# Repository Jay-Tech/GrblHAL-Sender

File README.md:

# GrblHAL Sender

A cross platform sender application for grblHAL, built using Avalonia UI and .NET.

The goal was an application that runs on a cheap mini PC, with a UI designed to be touch monitor friendly and usable without a mouse or keyboard.
</br>
---

</br>
## Runs on a portrait monitor as well as a landscape one

</br>
The layout follows the screen's orientation on its own — a 1920x1080 monitor gets the
landscape arrangement, a 1080x1920 one gets a portrait layout built for that shape. There is
nothing to set; rotate the display and restart.

Portrait is a different arrangement rather than a squeezed copy. The status strip splits over
two rows, the 3D view takes the full width, and the controls gather into a block along the
bottom — DRO and MDI on the left, work offsets, spindle and macros in the middle, jog pad on
the right — so everything sits within thumb reach on a rotated touchscreen.

Both layouts are assembled from the same panels, so a change to the jog pad or the DRO turns
up in both.
</br>
## GrblHAL Setting supports export and import 

</br>
## Supports Serial, TCP, or WebSocket connection protocols.  Push and hold "Connect" to setup connection type and Auto Connect on app launch if desired 

</br>
## Double clicking any Text Fields brings up virtual keyboard

</br>
## Host local Web Server for remote file upload 

</br>
## Supports Wireless Controller
 
</br>
## Supports a Wireless Pendant
A handheld MPG - handwheel, touch screen, three buttons - over ESP-NOW or WiFi.
Firmware and hardware are a companion project:
[Jay-Tech/WirelessPendant](https://github.com/Jay-Tech/WirelessPendant). See
[Wireless Pendant](#wireless-pendant) below.
</br>
# Settings Overview
## App

</br>
## Rapid-ATC

</br>
## Wireless Gamepad
  
</br>
## Pendant

</br>
Enable it, pick a transport, and bound what it may ask the machine for. Four of
these fail quietly if set wrong - see [Settings that fail quietly](#settings-that-fail-quietly).
</br>
## Web Server

</br>
## Macro Download and Upload Supported

# Tool Change

What the sender does at an `M6` depends on the controller's `$341` tool change mode. The
mode is read from the machine, so the relevant controls appear on their own — there is
nothing to configure in the app to match it. Changing `$341` while connected is picked up
as well, without a reconnect.

| `$341` | Mode | What the sender does |
|---|---|---|
| 0 | Normal | Pauses at the `M6`, acknowledges it, waits for **Start**. Your program is responsible for stopping the spindle, moving to the change position and restoring afterwards. |
| 1 | Manual touch off | As above, plus a **Touch Off** button |
| 2 | Manual touch off @ G59.3 | As mode 1, and needs the [tool setter position](#tool-setter-position-g593) set |
| 3 | Automatic touch off @ G59.3 | Pauses; the controller probes for itself on **Start**. Needs the tool setter position set. |
| 4 | Ignore M6 | No pause — the tool number is recorded and the program continues |

In every mode except 4 the machine reports `Tool` state, the sender acknowledges it
(`0xA3`) once on entry, and the program continues only when you press **Start**. It behaves
like an `M0` pause: the acknowledgement does not resume anything.

## Streaming stops at the tool change

The sender holds the rest of the file back when it sends an `M6`, and does not resume until
the controller reports the change finished. This matters because grblHAL rejects g-code
while a tool change is pending (`error:40`) — anything already sitting in its receive
buffer past the `M6` is discarded rather than queued, which on a short file can be the
whole remainder of the program.

While the job is paused there you can **jog freely** and use **MDI**, including as many
moves as you like; the file position does not advance and nothing is lost. Macro and probe
buttons stay disabled, since those would interleave into the program.

## Manual touch off (modes 1 and 2)

A **Touch Off** button appears beside the `TOOL` banner while the job is paused. It sends
`$TPW`, which probes the new tool and applies its length offset.

Every tool change: stop at the `M6` → change the tool → jog it over the reference surface →
**Touch Off** → **Start**.

## Tool length reference — do this before the job

`$TPW` applies the *difference* between this probe and the previous one, so it needs a
baseline. Set it once per session under **Probe → Tool Setter**, with the tool you are going
to zero the stock from:

- **Probe Here** — probes straight down from where the machine is standing; jog the tool
  over the setter first
- **Probe at G59.3** — retracts Z to machine zero, travels to the stored tool setter
  position, descends and probes

Either way the reference is set only if the probe actually makes contact. Then zero on the
stock and start the job, and every tool change from there needs nothing but **Touch Off**.

The panel says whether the controller currently holds a reference. On a good probe the tool
is backed off the trigger, and **Probe at G59.3** also returns to the X/Y it started from —
retracting Z to machine zero on the way and leaving it there, since the height it came from
may be down in the work.

> `$TLR` must follow a *successful* probe. Sent before one, or after a failed one, it clears
> the reference instead of setting it — which is why the app only issues it on a good probe.

Re-running it re-bases the datum onto whatever was last probed, so only do it deliberately —
after moving the tool setter, or re-zeroing against a different tool.

Touch plate thickness plays no part in this. The offset is a differential against the same
surface, so the thickness cancels out. Thickness only matters for setting workpiece Z zero,
which is a separate operation in the **Probe** dialog.

## Tool setter position (G59.3)

</br>
Modes 2 and 3 drive to the `G59.3` offset to reach the tool setter. Set it under
**Probe → Tool Setter**: jog the machine where you want it and store the position. X/Y and
Z are stored separately so neither overwrites the other by accident, and the stored value is
read back from the controller after each change so you can see what actually took effect.

> **The stored Z is where probing starts, not the tool setter surface.** The controller
> moves all three axes to `G59.3` and then probes downward by `$342`. Store Z at a safe
> clearance height above the setter — high enough for your longest tool, and no further
> above the setter than `$342`.

## Macro messages

Anything the controller says in words — including `(debug, ...)` output from a tool change
macro — is shown in the job panel, not only in the console. A macro that stops on
"manually unload the tool and unlock to continue" says so on screen.

# Probing

Every cycle probes twice: a fast pass at **Search Rate** to find the surface, then a slow one
at **Latch Rate** to measure it. **Distance** is how far a probe may travel looking for the
surface, and **Latch Dist** is how far it backs off between the two passes.

Probe moves are commanded in whatever units the display is set to, and the parser is handed
back the unit it was in when the cycle finishes.

Only the fields a cycle actually reads stay enabled, so what is greyed out is not being used.

## Probe type

| | |
|---|---|
| **Touch plate** | Work Z zero ends up the plate's thickness below where it triggered. |
| **3D probe** | **Diameter** compensates edge touches on the corner and centre cycles, and corrects the size they report. It plays no part in a Z probe — the ball meets a flat surface with its underside, directly beneath its centre, so where it triggers *is* the surface. |

## Z height

Position the probe above the surface and press **Probe Z**. Work Z zero is set at the surface,
and the stylus lifts clear by **Latch Dist** rather than being left resting on the work.

## Corner

Bring the probe to the corner, above the top face, and pick the corner that matches. Each leg
lifts to **Clearance Height**, moves clear of the stock on the axis it is about to probe while
stepping *in* on the other, drops by **Probe Depth**, and probes back toward the face. It
finishes lifted and standing over the corner it measured, which is now X0 Y0.

> **Probe Depth is measured from where you parked the stylus, not from the top of the stock.**
> If you sit 2mm above the face and want to touch 3mm down the side, Probe Depth is 5. Too
> shallow and the probe sweeps over the top of the edge and touches nothing.

The stand-off is Clearance Height, so Distance has to be comfortably larger than it for the
probe to reach the face.

## Center finder

**Bore** and **Rectangle** work from inside a hole or pocket. Position the probe roughly in
the middle, at the height you want it to touch at — these cycles never move Z, so Clearance
Height and Probe Depth do nothing and are greyed out. Distance has to cover the radius plus
however far off centre you started. Between legs the machine returns to the point you began
at, so a generous Distance is safe.

**Boss** and **Rect Boss** work from outside. Position the probe over the middle of the
feature and above its top face. Each leg stands off by half the approximate size plus
Clearance Height, drops by Probe Depth, and probes inward. A round boss takes one size; a
rectangular one takes a width and a height separately.

> **Keep Clearance Height larger than your eyeballing error.** Starting off centre adds to the
> stand-off on the far side and takes it away on the near side, so being out by more than the
> clearance puts the stylus over the feature when it drops. Under-estimating the approximate
> size eats the same margin. Over-estimating is safe — the probe simply travels further.

Y is probed from the X you started at rather than the measured centre. That is exact for a
rectangle, where a flat face reads the same anywhere along it, and leaves a small error on a
bore or boss if you started well off centre. Run it twice if that matters.

## When a probe misses

The cycle stops at the first missed contact rather than carrying on from a position that means
nothing, and says which datum it did not set. Nothing is written on a failure. A tool length
reference is the one worth spelling out: `$TLR` is not sent, so whatever reference the
controller was holding is still intact.

# G-code Events

</br>
Pre and post commands can be injected around any g-code event, configured under
**Utility → G-code Events**. The original use case is lifting a dust shoe out of the way for
a tool change or a homing cycle, but nothing about it is specific to that.

Each rule has a trigger and the commands to wrap it with:

- **Trigger** — one or more commands, comma separated, e.g. `$H,G28`. A `$` command matches
  as a prefix, so `$H` also catches `$HX`. A single word matches by value, so `M6` catches
  `T3M6` and `M06` but not `M61`.
- **Pre / Post** — commands to send before and after the trigger, separated by `|` for more
  than one. `{T}` inserts that word's value from the triggering line, `{LINE}` the whole line.
- **Job / MDI** — whether the rule applies to a streamed file, to commands you issue by
  hand, or both.

Rules are applied when a file is loaded, so reload the file after editing one.

## Getting the timing right in a job

grblHAL executes `M64`/`M65` when it *parses* them, which during a job is well ahead of the
cutting point — so a plain `M65P0` before an `M6` fires many blocks early, while the spindle
is still down and cutting.

A dwell forces the planner to drain before continuing, so putting one *first* moves the
output change to the right moment:

| | |
|---|---|
| `M65P0\|G4P0.2` | lifts early, then waits — wrong |
| `G4P0.1\|M65P0` | waits for the cut to finish, then lifts — right |

Aux output buttons follow these commands wherever they come from, so a rule that toggles a
pin moves the matching button too.

# Shop Outputs

</br>
The sender can switch relays for shop lights, dust collection — anything you would otherwise
reach over and flip. Configured under **Utility → GPIO**, and off by default: nothing is
driven until you enable it.

This is for convenience, not safety. E-stop and safety door belong hardwired to the
controller, where they do not depend on a userland app being responsive. Nothing here is
time-critical either — the outputs settle in the second or so after the machine state
changes, which is fine for a vacuum and useless for an interlock.

Worth knowing why this exists alongside the controller's own aux outputs: those are driven by
`M62`/`M64`, which grblHAL executes when it *parses* them, well ahead of the cutting point
during a job. That is why the [G-code Events](#getting-the-timing-right-in-a-job) section
needs dwell-first ordering. A shop output is not in the g-code stream at all, so "run the vac
while the spindle is cutting, then for fifteen seconds after" needs no such trickery.

## Where the outputs live

| Device | Needs | Notes |
|---|---|---|
| **PiHeader** | A Raspberry Pi | The Pi's own 40-pin header. No extra hardware. |
| **UsbSerial** | A microcontroller on USB | Works on any host the app runs on — mini PC, Mac, or a Pi. |

The USB option exists because the header option only ever serves installs that run on a Pi.
Both behave identically once configured; everything below applies to either unless it says
otherwise.

## Off / Auto / On

Each output is a button in the bottom-left of the workspace, above the controller's aux
output buttons. Tapping it cycles the mode. The ring around the button shows whether the
relay is actually energised, which is not the same thing as the mode — an output sitting in
Auto reads `AUTO` whether or not it happens to be on right now.

| Mode | Behaviour |
|---|---|
| **Auto** | Follows the machine. Skipped in the cycle for outputs with no follow source. |
| **On** | Held on regardless of the machine. This is the one for cleanup before and after a job. |
| **Off** | Held off. Takes effect immediately — it does not wait out the off delay. |

Unlike the aux output buttons these stay live while the controller is disconnected, because
running the vacuum with the machine idle or unplugged is most of the point of the manual mode.

## What Auto follows

| Follows | Source |
|---|---|
| **Spindle** | The controller's accessory (`A:`) field |
| **Connected** | Whether the controller is connected — reasonable for lighting |
| **None** | Manual only; the output has no Auto mode |

Spindle state is taken from the status report rather than by watching for `M3`/`M5` in the
stream, so it reflects what the machine is actually doing. It picks up a spindle you started
by hand from the console, and it stays honest when a job aborts part way through, where the
file position tells you nothing useful.

## Spindle threshold — for ATC tool changes

**Min RPM** is the speed at or above which the spindle counts as running. Leave it at `0` and
any spindle-on state qualifies.

It exists for automatic tool changers. A RapidChange ATC and similar turn the spindle at a
low speed to thread and unthread the holder — a genuine spindle-on state with no cutting and
no chips. Without a threshold the dust collector fires at every tool change. Set Min RPM
above your changer's speed and below your cutting speed, and tool changes stop triggering it.

The comparison uses the *programmed* speed — the `S` word from the status report — not tacho
feedback. That steps cleanly when a macro commands a speed, rather than sweeping through the
threshold on every spin-up and spin-down.

Speed is watched as well as direction, which matters at the end of a change: the program
returns to cutting speed with the spindle never stopping, so the direction does not change
across it. Dropping back under the threshold mid-job behaves like the spindle stopping and
goes through the off delay, so a change that fits inside the delay window never moves the
relay at all.

> The threshold reads whatever `S` value is currently in force, so a tool change macro that
> sets a low `S` and does not restore it will hold the output off until the program commands
> a speed again.

## Off delay

An output in Auto stays on for **Off Delay** seconds after its source goes inactive. This is
doing two jobs. It clears the hose of chips still in flight after a cut, and — more
importantly — it stops a program full of tool changes and `M5`/`M3` pairs from dropping and
re-closing a contactor every few seconds. Any fresh demand inside the window cancels the
pending switch-off, so a run of tool changes collapses into one continuous run.

Fifteen seconds is a sensible starting point. An explicit **Off** ignores the delay entirely.

## Wiring

On a Pi, pins are **BCM numbers**, 2–27. Avoid 2/3 (I²C, permanently pulled up), 7–11 (SPI)
and 14/15 (UART); 17, 22, 23, 24, 25, 27 are all clean, and the **Add Output** button hands
out unused ones in that order.

On a USB device, pins are that board's own numbering — `GP` numbers on a Pico — and the valid
range is reported by the device itself rather than assumed.

**Prefer an active-high relay board.** BCM 9–27 boot with a pull-down, so an active-high
board reads *off* while the Pi boots, while the app is starting, and after it exits or
crashes — the fail-safe state costs nothing. An active-low board inverts all of that and
wants an external pull-up to stay safe. Set **Active Hi** to match whichever you have.

Do not drive a relay coil from a pin directly; use an opto-isolated module, a MOSFET driver
or an SSR. And size the switching for the load — a shop vacuum's inrush will weld the
contacts of a generic 10 A relay board sooner or later, so drive a proper contactor with it.

## Pi header setup

The header GPIO is reached through libgpiod. Installing the tools package pulls the right
runtime library whichever release you are on, which matters because the library package was
renamed between Debian releases (`libgpiod2` on Bookworm, `libgpiod3` on Trixie):

```
sudo apt install gpiod
sudo usermod -aG gpio $USER
```

Log out and back in for the group to take effect. `gpiodetect` should report the 40-pin
header as `gpiochip0 [pinctrl-rp1]` on a Pi 5.

If the app cannot reach the hardware it says so on the GPIO config tab rather than failing
silently or crashing — the message is the underlying error, so it will tell you whether it is
a driver or a permissions problem. With no device reachable the outputs still appear and
toggle but switch nothing, which keeps the app usable for development.

## USB device setup

The device runs the PICOGPIO protocol, specified in
[docs/pico-gpio-protocol.md](docs/pico-gpio-protocol.md). A MicroPython reference
implementation for a Raspberry Pi Pico is in [firmware/pico/main.py](firmware/pico/main.py) —
about a hundred lines, and enough to use in earnest.

Flash MicroPython onto the board, then copy the script to it as `main.py` so it runs on boot
and owns the USB serial port instead of the REPL:

```
pip install mpremote
mpremote connect COM10 fs cp firmware/pico/main.py :main.py
mpremote connect COM10 reset
```

Then pick **Device: UsbSerial** and select the port. **Close any IDE connected to the board
first** — a serial port can only be held by one program, and Thonny in particular keeps the
handle after you disconnect, which shows up as "access is denied". **Reconnect** retries
without restarting the app, and also covers unplugging the device mid-session.

The app never scans ports. A grblHAL controller and a Pico both enumerate as `/dev/ttyACM*`
on Linux and are indistinguishable by name, so the port is always chosen explicitly and
nothing is written until the device identifies itself.

### The device watchdog

The protocol requires the device to drive every output inactive if the host stops talking to
it — five seconds in the reference implementation. This covers what the app cannot: the
application crashing, the cable being pulled, or the host sleeping while USB power stays up.
A host-side "turn everything off on exit" only works when the exit is orderly.

That makes a USB device arguably safer than the Pi header, where an app that dies leaves the
pins to their boot-time pull-down.

## Behaviour worth knowing

Losing the connection drops any output following the spindle. Status reports stop arriving
when the link goes down, so the last known spindle state is stale — left alone, a spindle
that happened to be running at that moment would hold the dust collector on indefinitely.

Closing the app drives every output off before it exits, so quitting cannot leave the vacuum
running. The mode each output was left in is saved, with one exception: an output that
follows something never comes back **On** after a restart. Returning from a power cut with
the dust collector latched on is not what anyone means by remembering a setting. Manual-only
outputs do restore On, so shop lights come back as you left them.

# Wireless Pendant

A handheld MPG pendant - handwheel, touch screen, three buttons - that talks to
this application rather than to the controller. The firmware, the hardware and
the printed enclosure are a companion project:
**[Jay-Tech/WirelessPendant](https://github.com/Jay-Tech/WirelessPendant)**.

It goes through the sender deliberately. grblHAL's telnet server accepts exactly
one client and this app already holds it, so a pendant cannot have a session of
its own; and on an SLB the controller sits on an isolated subnet with no route
from the shop WiFi. Coming through the sender works with any controller and keeps
one arbiter of the command queue, which is what GRBL needs regardless.

## Two transports, and both run at once

| | |
|---|---|
| **ESP-NOW** | the pendant talks to a small receiver board plugged into this PC, which appears here as a serial port. No network, no credentials |
| **WiFi** | the pendant joins the shop network and opens a TCP session to the port set on the Pendant tab |

Both carry the same newline-delimited JSON, so nothing above the transport knows
which one a pendant arrived on, and naming a receiver port does not disable the
network listener.

**One pendant drives the machine at a time, and the newest wins.** That is not
about arbitrating between two operators - it is about one operator whose pendant
has appeared twice. Over WiFi the older connection is usually a stale half-open
socket left by a lost link, which TCP can take minutes to give up on; over
ESP-NOW it is a handheld just switched on while the WiFi one is still nominally
connected. Refusing the newcomer in either case locks the operator out of the
machine while a dead connection times out.

## The receiver's port is never scanned for

Pick it explicitly. A grblHAL controller and a receiver board both enumerate as
anonymous USB serial devices and cannot be told apart by name, and pendant JSON
written at a controller is at best noise in its console. Leave it on *(none)* if
no receiver is fitted; the WiFi listener still runs.

## Settings that fail quietly

Most of the Pendant tab explains itself. These four do not:

| Setting | Default | Why it matters |
|---|---|---|
| **Max feed rate** | 12000 | Set this to the machine's own maximum jog rate. The pendant already limits itself per axis and per step, and 12000 is the most it can ever ask for - so anything lower **silently discards feed the operator asked for**. A previous default of 5000 clamped both coarse steps, which is felt as the wheel going heavy near the top of its range and reported as nothing. |
| **Min gap between jogs** | 10 ms | Must stay **below** the pendant's 20 ms tick. Set equal, the two free-run and beat against each other: some windows carry two messages and some carry none, and an empty window is a gap the machine decelerates into. Set above, messages merge back into the long blocks the short tick exists to avoid, which halves the count the planner can chain - and chaining is what holds a feed. This is also the only place backpressure can be applied, since the pendant cannot see the controller's planner. |
| **Max jog per message** | 50 mm | Bounds a corrupted detent count, and clamps rather than discards. At a 20 ms tick and the 12000 mm/min ceiling a dispatch window legitimately carries 4 mm, so this leaves an order of magnitude of headroom. |
| **Allow pendant to zero an axis** | off | Zeroing rewrites the work offset. Off by default so a mis-hit button on a handheld cannot lose your datum. |

**Enabling the pendant takes an app restart.** Two more worth knowing about:

- **Client timeout**, 15 s, stands the pendant down when it goes quiet. The
  pendant pings every few seconds, so silence means it has gone away without
  saying so - a case TCP alone can take minutes to notice, and a serial receiver
  cannot notice at all, since its port stays open whether or not a handheld is
  switched on. Zero disables it.
- **Echo pendant jogs to console** is diagnostic only. Jogs arrive fifty times a
  second, which fills the console to its cap within seconds and then costs a UI
  update on every status tick - felt as jerk partway through a long move.

## The receiver's DTR and RTS are configurable, and the board decides

Behind a USB-UART bridge these are not flow control at all: they are wired to EN
and IO0 through the auto-reset circuit, so driving them on open resets the chip
or drops it into its bootloader. An ESP32-S3 has native USB and no such circuit,
but a firmware using TinyUSB CDC may read DTR as "a terminal is attached" and go
quiet without it. The two failure modes want opposite settings, which is why this
is configuration rather than a constant.

Change them only against an observed symptom - a receiver that wedges when the
sender starts, or one that opens cleanly and then never says anything.

# Testing status

Runs on Windows and on Linux including the Pi 5, on landscape and portrait displays.

Verified on hardware:
- The portrait layout on a 1080x1920 screen, and the landscape one after the panels were
  refactored to be shared between the two
- Tool change streaming — the job holds at the `M6`, survives jogging during the pause, and
  resumes cleanly on **Start**
- Manual touch off (`$341=1` / `2`) — the **Touch Off** button and `$TPW`, including jogging
  to the setter and back mid-change
- Automatic touch off (`$341=3`)
- `M6T<n>` from the MDI with no file loaded
- Tool length reference and tool setter position (`G59.3`), including the return to the X/Y
  the probe started from
- Changing `$341` while connected — the controls follow without a reconnect
- G-code event injection around a tool change, including the dwell-first ordering
- GPIO shop outputs on a Pi 5 — a relay on BCM 17 following the spindle in Auto, and the
  manual On/Off override, with no spurious activation across two boot cycles
- Shop outputs over USB — a Pico running the MicroPython reference firmware, driven from a
  Windows host: identify handshake, pin claim and switching
- Serial connection and reconnection
- Single instance guard on Linux
- The probe cycles with a 3D probe — workpiece Z zero, all four corners, and centre finding
  inside a bore and outside a boss

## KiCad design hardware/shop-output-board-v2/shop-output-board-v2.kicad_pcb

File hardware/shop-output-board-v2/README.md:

# Shop Output Board v2

> ### On the shelf as of 2026-08-06 — see [commercial-alternatives.md](../commercial-alternatives.md)
>
> Bought Pico relay boards cover the shop-outputs use case for a fraction of what this costs
> to build, with the relays already on them and an enclosure round the outside. This board was
> routed, verified and had its JLCPCB files prepared before that turned up — all of which is
> still here and still correct. It just is not the thing to order.
>
> Worth knowing if you come back to it: the design is sound, `JlcLab/` is ready bar the LCSC
> codes and F1 sourcing, and **it has never been bench-tested**. Start at
> [bench-test.md](../shop-output-board/bench-test.md) if that ever changes.

Four-channel opto-isolated high-side switch board. **70 × 92 mm against v1's 150 × 115 —
64% less area**, same circuit per channel.

**Generated and placed, not routed.** DRC is clean on the placement; the routing is the work
left to do, exactly as v1 was at this stage.

## What changed from v1, and what did not

**Unchanged: the entire channel circuit.** Same optocoupler, same AO3401A, same 8.2 V gate
clamp, same resistor values. That is the point — [v1's bench-test procedure](../shop-output-board/bench-test.md)
validates this board too, and the one part of the design nobody has watched work does not get
disturbed by a packaging exercise.

| | v1 | v2 |
|---|---|---|
| Channels | 8 | 4 |
| Board | 150 × 115 mm | **70 × 92 mm** |
| Parts | 84 | 47 |
| Output terminals | two 6-way | one 6-way (4 out + 2 gnd) |
| Bulk cap C1 | 100 µF, 8 × 10.5 mm | 47 µF, 6.3 × 7.7 mm |
| MCU | socketed Pico | socketed Pico — *unchanged* |
| F1 | 1812, 1.1 A / 24 V | same |

**The Pico stays.** Swapping it for a thumb-sized RP2040 module was the original motivation
for v2 and it turned out to be worth almost nothing: at four channels the channel bank is
51.4 mm wide and a Pico's pad span is 48.3 mm, so the Pico already fits inside the width the
channels demand. On height it buys 3.78 mm. See [v2-layout.md](../shop-output-board/v2-layout.md)
for the full working. Keeping it means no new footprint, no pin map, no firmware change.

## The channel, rearranged

This is where the height saving comes from. v1 stacks all seven isolated-side parts in one
column 35 mm tall; v2 splits them into two sub-columns grouped by **net**:

```
                 cx-4              cx+4
  y=41.19          ▀▀▀ opto pins 3,4 ▀▀▀      (centreline)
  y=44      ═══════════ V+ rail ═══════════
  y=47             Q                 R2       Q source → rail; R2 → opto above
  y=51             R3                D
  y=55             R4                R1
  y=59             LED
```

**Left column is everything touching `OUT`, right column is everything touching `GATE`.**
They meet only at Q, which is why Q sits at the top of the left column — its source reaches
the rail in 2 mm, its gate faces right toward the gate column, and its drain has a clear run
straight down its own column to the terminal. R2 sits opposite it, directly under the
optocoupler it feeds.

Channel height: **19 mm, against v1's 35 mm.**

## Regenerating

```
python generate_schematic.py
kicad-cli sch erc --output erc.rpt --severity-error shop-output-board-v2.kicad_sch
kicad-cli sch export netlist --output netlist.net shop-output-board-v2.kicad_sch
python verify_netlist.py

python generate_pcb.py
kicad-cli pcb export ipcd356 --output pads.d356 shop-output-board-v2.kicad_pcb
python verify_pcb.py
kicad-cli pcb drc --refill-zones --output drc.rpt --severity-error shop-output-board-v2.kicad_pcb
```

Channel count comes from `CHANNEL_GP` in `generate_schematic.py` — shortening that list is
the whole change. Everything else derives from it.

`generate_pcb.py` has **no `--route` flag**. v1 carried one that never got past 113 DRC
violations; a half-routed board is worse to inherit than an unrouted one, so it is not
carried forward.

## State

| | |
|---|---|
| Schematic | generated, ERC clean (0 violations) |
| Netlist | 58 nets, 47 parts, all assertions pass |
| Placement | generated, 99 pads match KiCad's own coordinates to 0.05 mm |
| Barrier | 16 opto pads correct side; **0 traces, 0 vias, 0 zone vertices** in y=34–39 |
| Routing | **done by hand** — 198 segments, 11 vias, 0 unconnected |
| Mounting | 3 × Ø3.2 mm NPTH at (4,4), (4,88), (66,4), each with a Ø7.6 copper keepout |
| DRC | 15 violations, **all `output net spacing`** — see below |
| Bench verification | none — inherited from v1, which has not been tested either |

## Mounting holes and the isolation barrier

The holes straddle both domains: (4,4) and (66,4) sit in the `PICO_GND` pour, (4,88) in
`ISO_GND`. Mounted on a metal panel with metal standoffs, the chassis ties all three together
— so if any screw head reaches the pour it is sitting on, **the two ground domains are
bridged and the isolation this board exists for is gone.**

As first routed, copper came within 0.34–0.50 mm of the hole edges, which every standard M3
head overlaps:

| Hardware | Head reach | Was | Now |
|---|---|---|---|
| M3 socket cap Ø5.5 | 2.75 mm | contact | clears 1.04 mm |
| M3 pan head Ø5.6 | 2.80 mm | contact | clears 0.99 mm |
| M3 countersunk Ø6.0 | 3.00 mm | contact | clears 0.79 mm |
| M3 + flat washer Ø7.0 | 3.50 mm | contact | clears 0.29 mm |

Fixed with a **Ø7.6 mm copper keepout** (48-gon, R3.8) on both layers at each hole, blocking
pour, tracks and vias. Copper now sits 3.79 mm from each hole centre, measured on a
zone-refilled Gerber plot rather than the stored fill.

**DRC cannot catch this class of fault** — it has no concept of a screw head. If you move a
mounting hole, re-check it by hand.

The holes were also Ø3.00, which is zero clearance for an M3 (its major diameter *is* 3.0 mm,
so the screw will not pass). Now Ø3.2, the standard close fit.

## Net classes: set them, or DRC is lying to you

`shop-output-board-v2.kicad_pro` carries `Logic` and `Isolated` as `netclass_patterns`. The
custom rules in `shop-output-board-v2.kicad_dru` key on exactly those names.

Until they were set, **DRC reported 0 violations on a board with 19 of them**, because every
custom rule silently matched nothing. The barrier happened to be clean — verified by hand —
but nothing was checking it. Confirmed armed by injecting a deliberate barrier-crossing trace
into a scratch copy: caught as `rule 'isolation barrier' clearance 5.0000 mm; actual 0.1250 mm`.

If you ever edit net classes in Pcbnew, remember **File → Save Project**, not Ctrl+S.

## The 15 remaining violations

All are the `output net spacing` rule: 0.20 mm actual against the 0.40 mm the rule asks for,
across four pairs where the outputs fan into J2.

| Pair | Region |
|---|---|
| OUT1 ↔ OUT2 | x 19–60, y 63–78 |
| OUT1 ↔ V+ | x 4–50, y 54–63 |
| OUT2 ↔ OUT3 | x 35–60, y 54–78 |
| OUT3 ↔ OUT4 | x 52–61, y 55–71 |

This is a **margin** rule, not a correctness one — it exists to give the output nets room
against inductive kick from relay coils at the far end of the wiring. The board is
electrically fine at 0.20 mm. Either re-route that fan-in with 0.4 mm spacing (there is room:
0.5 mm tracks on a 3.81 mm terminal pitch need only 0.9 mm), or relax the rule deliberately
and write down why. Do not leave it failing silently.

## Before this goes anywhere

**v2 inherits v1's entire channel circuit, so a v1 bench failure is a v2 failure.** There is
no sense routing this, let alone fabbing it, until one channel has been proven on a
breadboard. That procedure is [bench-test.md](../shop-output-board/bench-test.md).

The indicator LED polarity bug found in v1 on 2026-08-05 is fixed here from the start — the
node from R4 lands on pin 2 (anode), and `verify_netlist.py` asserts it in that direction.

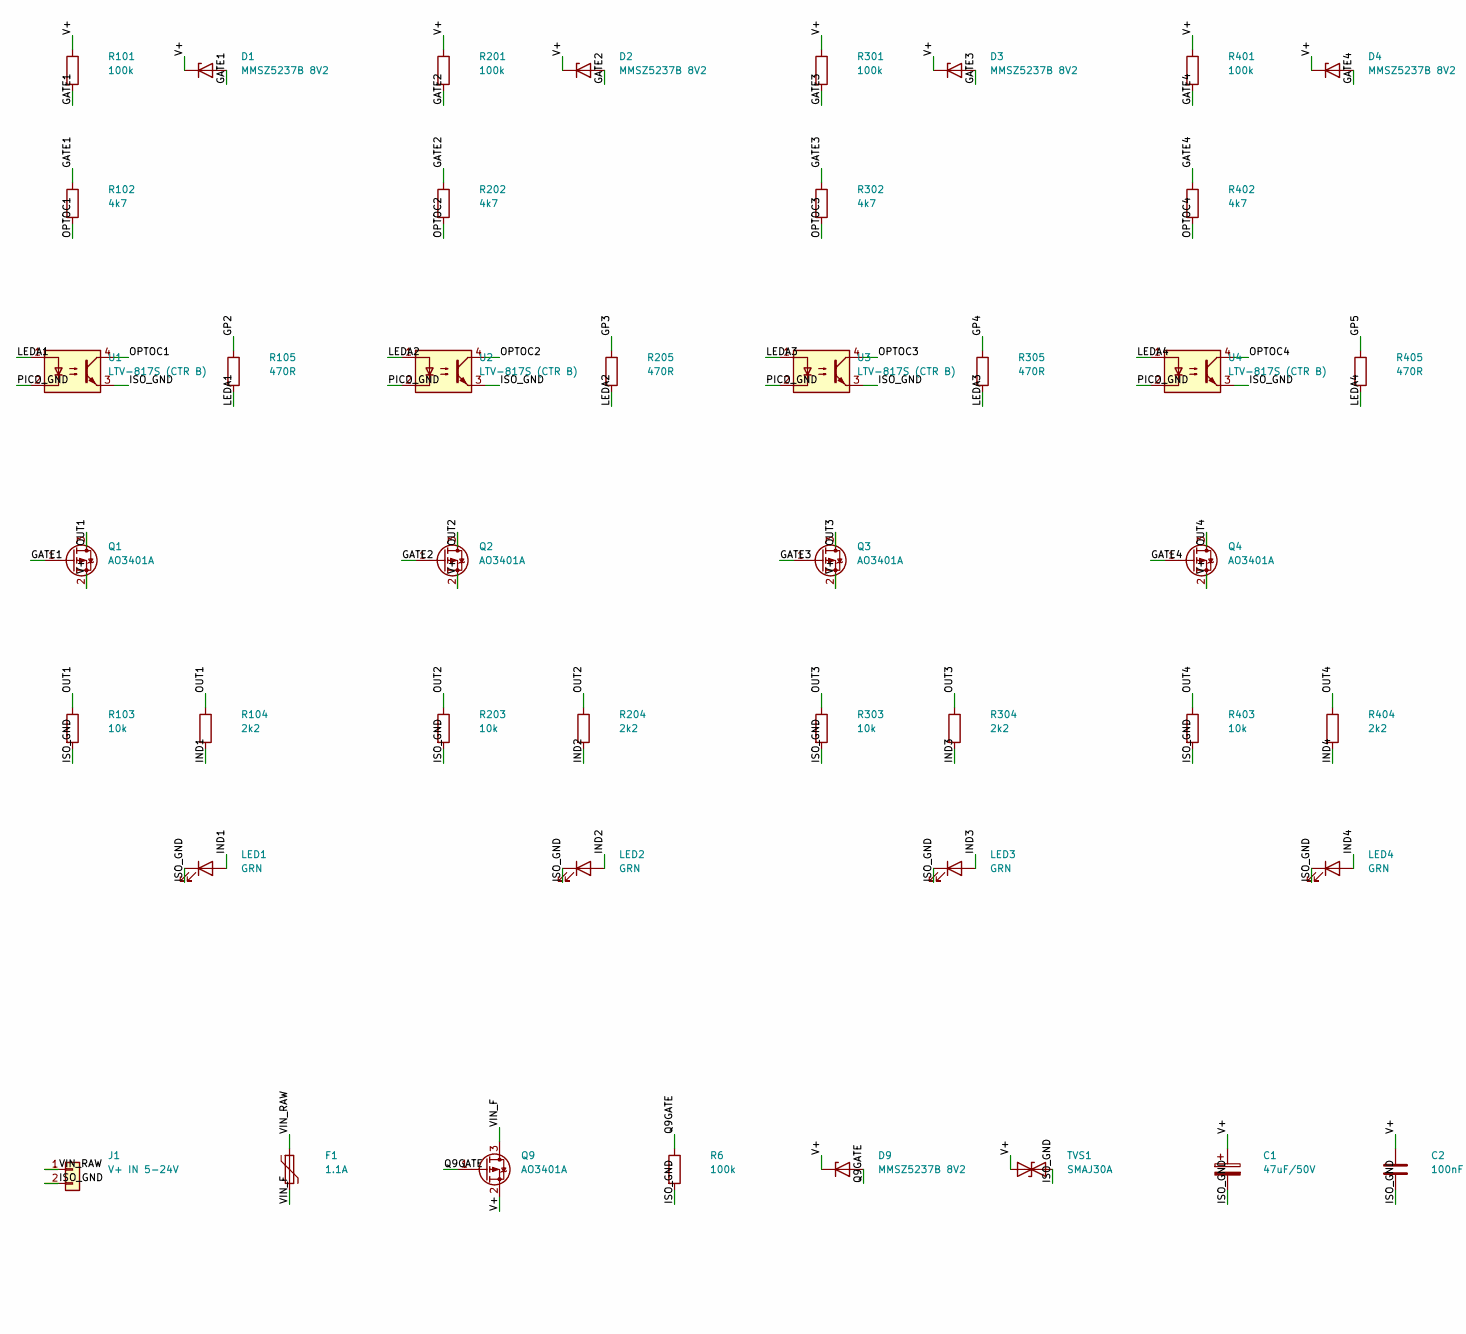
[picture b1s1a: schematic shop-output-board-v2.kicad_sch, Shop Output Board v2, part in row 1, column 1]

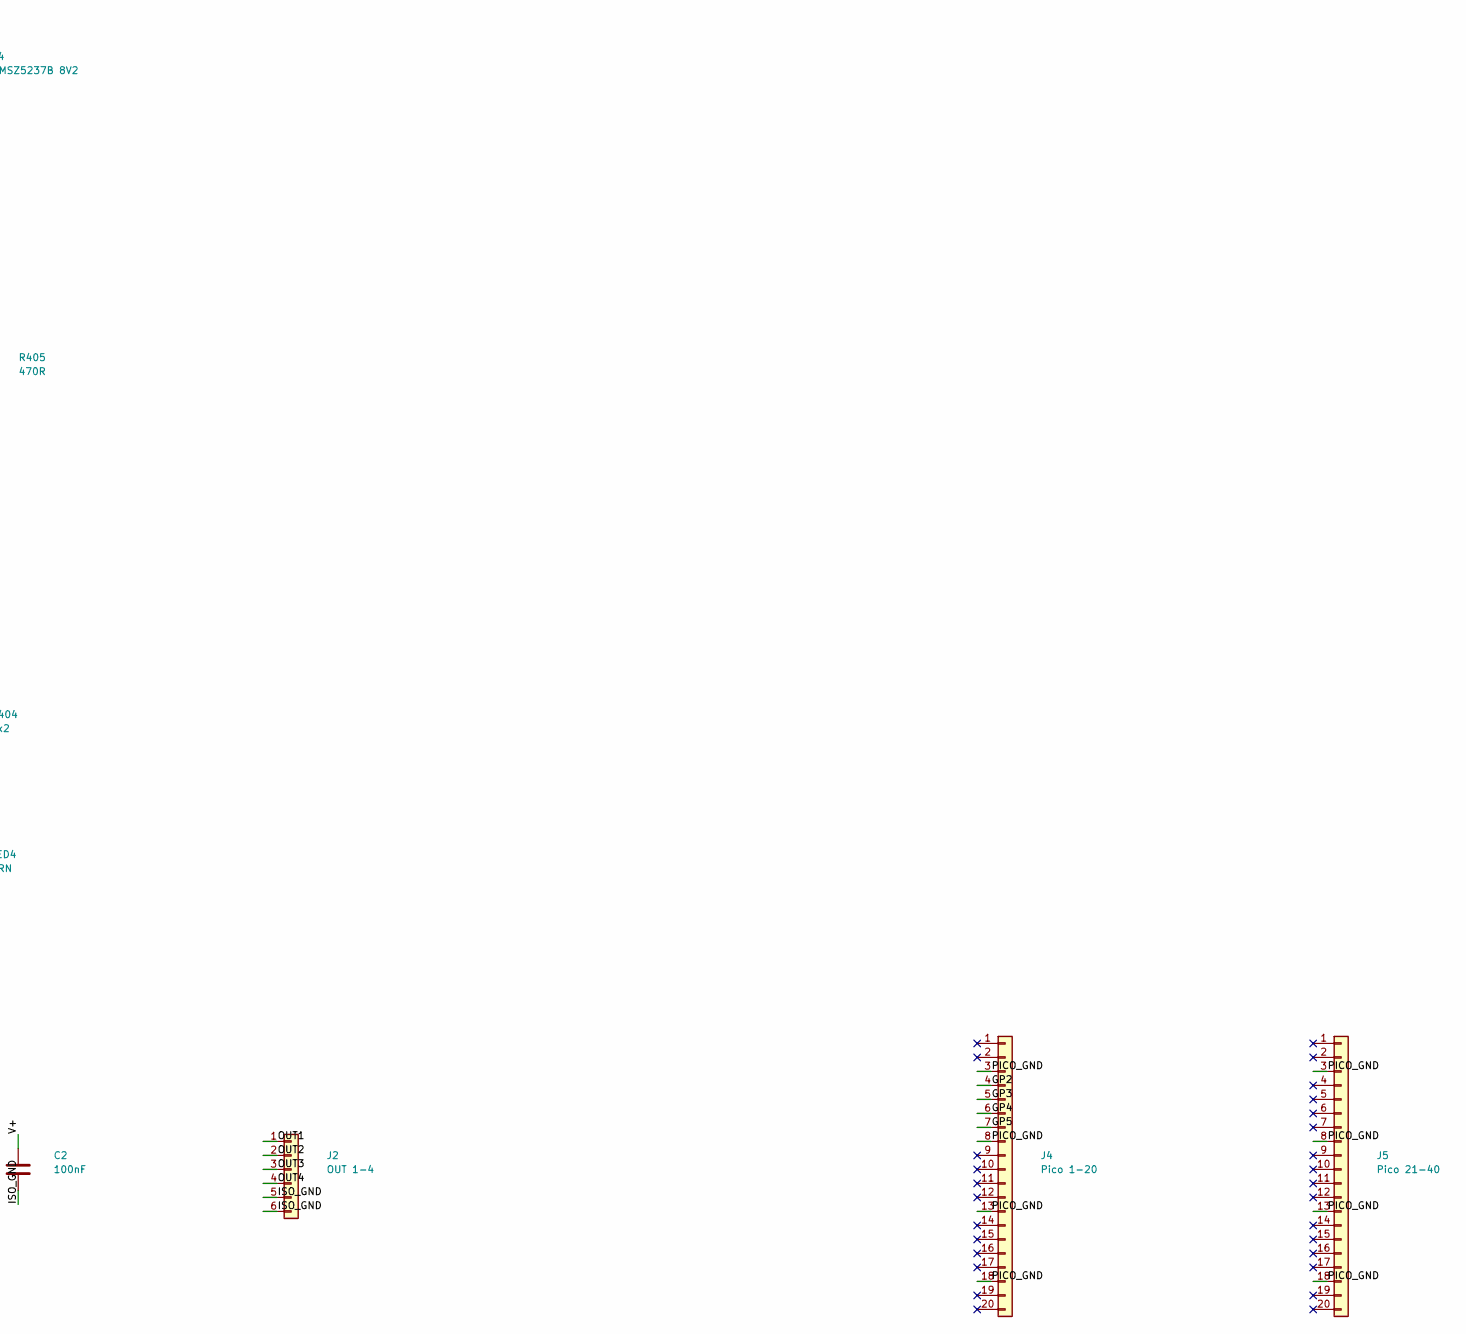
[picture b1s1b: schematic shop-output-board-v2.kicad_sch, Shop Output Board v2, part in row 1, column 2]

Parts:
C1: 47uF/50V; CP_Elec_6.3x7.7; MPN EEE-FK1H470XP
C2: 100nF; C_0805_2012Metric; MPN CL21B104KBCNNNC
D1, D2, D3, D4, D9: MMSZ5237B 8V2; D_SOD-123; MPN MMSZ5237B-7-F
F1: 1.1A; Fuse_1812_4532Metric; MPN MF-MSMF110/24X-2
J1: V+ IN 5-24V; TerminalBlock_Phoenix_MKDS-1,5-2-5.08_1x02_P5.08mm_Horizont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; MPN 1729128
J2: OUT 1-4; TerminalBlock_Phoenix_MKDS-1-6-3.81_1x06_P3.81mm_Horizontal; MPN 1727052
J4: Pico 1-20; PinSocket_1x20_P2.54mm_Vertical; MPN PPTC201LFBN-RC
J5: Pico 21-40; PinSocket_1x20_P2.54mm_Vertical; MPN PPTC201LFBN-RC
LED1, LED2, LED3, LED4: GRN; LED_0805_2012Metric; MPN LTST-C170KGKT
Q1, Q2, Q3, Q4, Q9: AO3401A; SOT-23; MPN AO3401A
R6, R101, R201, R301, R401: 100k; R_0805_2012Metric; MPN RC0805FR-07100KL
R102, R202, R302, R402: 4k7; R_0805_2012Metric; MPN RC0805FR-074K7L
R103, R203, R303, R403: 10k; R_0805_2012Metric; MPN RC0805FR-0710KL
R104, R204, R304, R404: 2k2; R_0805_2012Metric; MPN RC0805FR-072K2L
R105, R205, R305, R405: 470R; R_0805_2012Metric; MPN RC0805FR-07470RL
TVS1: SMAJ30A; D_SMA; MPN SMAJ30A
U1, U2, U3, U4: LTV-817S (CTR B); SOP-4_7.5x4.1mm_P2.54mm; MPN LTV-817S-TA1-B

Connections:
GATE1: D1.2 (A), Q1.1 (G), R101.2, R102.1
GATE2: D2.2 (A), Q2.1 (G), R201.2, R202.1
GATE3: D3.2 (A), Q3.1 (G), R301.2, R302.1
GATE4: D4.2 (A), Q4.1 (G), R401.2, R402.1
GP2: J4.4, R105.1
GP3: J4.5, R205.1
GP4: J4.6, R305.1
GP5: J4.7, R405.1
IND1: LED1.2 (A), R104.2
IND2: LED2.2 (A), R204.2
IND3: LED3.2 (A), R304.2
IND4: LED4.2 (A), R404.2
ISO_GND: C1.2, C2.2, J1.2, J2.5, J2.6, LED1.1 (K), LED2.1 (K), LED3.1 (K), LED4.1 (K), R6.2, R103.2, R203.2, R303.2, R403.2, TVS1.2 (A2), U1.3, U2.3, U3.3, U4.3
LEDA1: R105.2, U1.1
LEDA2: R205.2, U2.1
LEDA3: R305.2, U3.1
LEDA4: R405.2, U4.1
OPTOC1: R102.2, U1.4
OPTOC2: R202.2, U2.4
OPTOC3: R302.2, U3.4
OPTOC4: R402.2, U4.4
OUT1: J2.1, Q1.3 (D), R103.1, R104.1
OUT2: J2.2, Q2.3 (D), R203.1, R204.1
OUT3: J2.3, Q3.3 (D), R303.1, R304.1
OUT4: J2.4, Q4.3 (D), R403.1, R404.1
PICO_GND: J4.3, J4.8, J4.13, J4.18, J5.3, J5.8, J5.13, J5.18, U1.2, U2.2, U3.2, U4.2
Q9GATE: D9.2 (A), Q9.1 (G), R6.1
V+: C1.1, C2.1, D1.1 (K), D2.1 (K), D3.1 (K), D4.1 (K), D9.1 (K), Q1.2 (S), Q2.2 (S), Q3.2 (S), Q4.2 (S), Q9.2 (S), R101.1, R201.1, R301.1, R401.1, TVS1.1 (A1)
VIN_F: F1.2, Q9.3 (D)
VIN_RAW: F1.1, J1.1

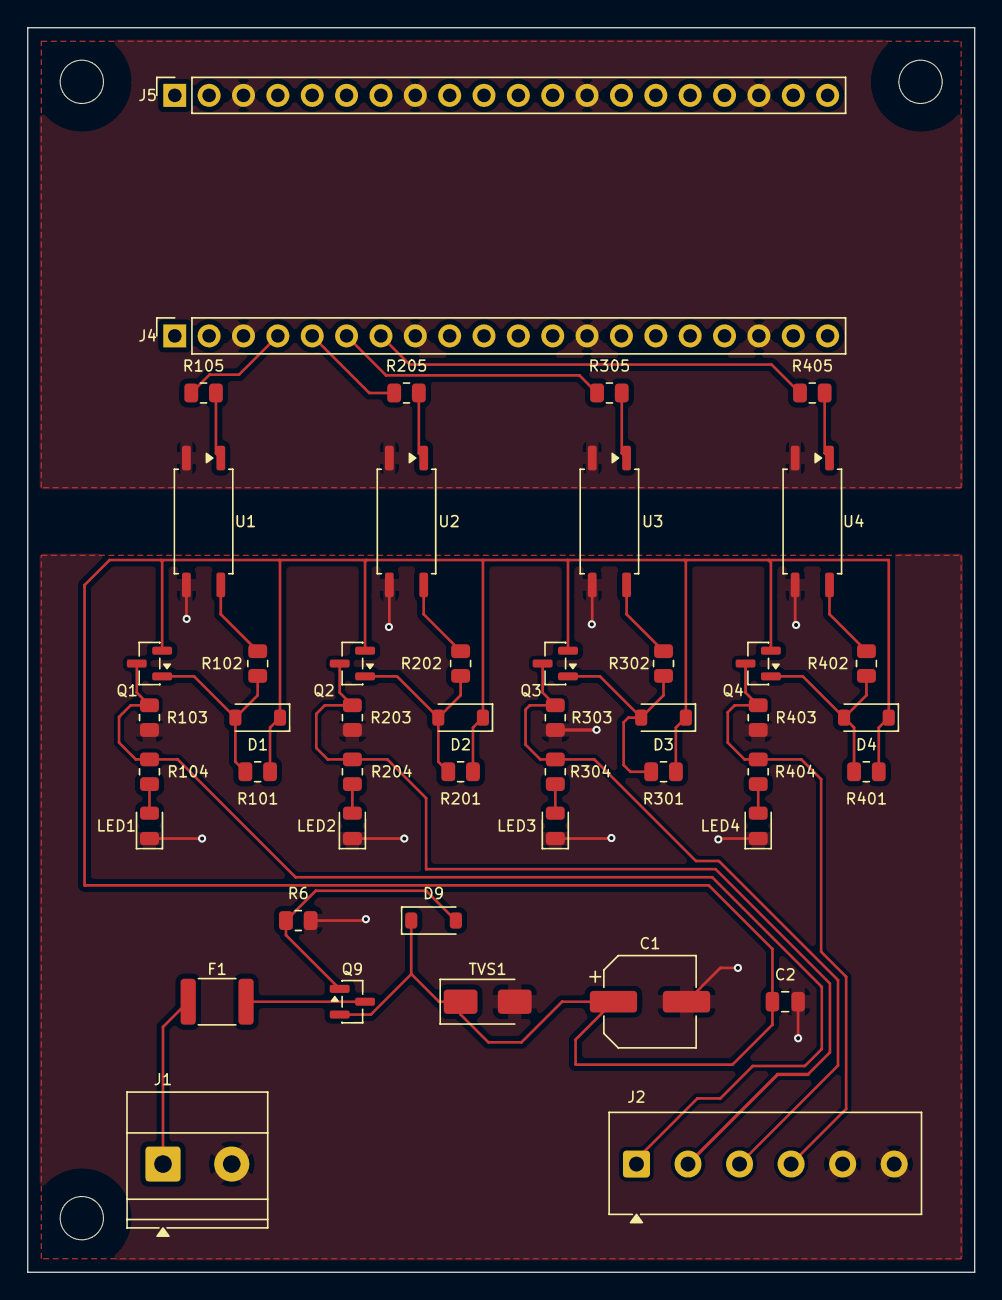
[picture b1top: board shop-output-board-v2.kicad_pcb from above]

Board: 2 copper layers, 70.0 x 92.0 mm, 47 parts (0 on the bottom side), 30 nets.

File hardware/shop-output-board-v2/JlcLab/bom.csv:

Comment,Designator,Footprint,LCSC Part #,MPN,Manufacturer,Quantity
47uF/50V,C1,CP_Elec_6.3x7.7,C970679,EEE-FK1H470XP,Panasonic,1
100nF,C2,C_0805_2012Metric,C49678,CL21B104KBCNNNC,Samsung,1
MMSZ5237B 8V2,"D1,D2,D3,D4,D9",D_SOD-123,C500790,MMSZ5237B-7-F,Diodes Inc,5
1.1A,F1,Fuse_1812_4532Metric,,MF-MSMF110/24X-2,Bourns,1
GRN,"LED1,LED2,LED3,LED4",LED_0805_2012Metric,C2297,LTST-C170KGKT,Lite-On,4
AO3401A,"Q1,Q2,Q3,Q4,Q9",SOT-23,C15127,AO3401A,Alpha & Omega,5
100k,"R6,R101,R201,R301,R401",R_0805_2012Metric,C17407,RC0805FR-07100KL,Yageo,5
4k7,"R102,R202,R302,R402",R_0805_2012Metric,C17673,RC0805FR-074K7L,Yageo,4
10k,"R103,R203,R303,R403",R_0805_2012Metric,C17414,RC0805FR-0710KL,Yageo,4
2k2,"R104,R204,R304,R404",R_0805_2012Metric,C17520,RC0805FR-072K2L,Yageo,4
470R,"R105,R205,R305,R405",R_0805_2012Metric,C17710,RC0805FR-07470RL,Yageo,4
SMAJ30A,TVS1,D_SMA,C134979,SMAJ30A,Littelfuse,1
LTV-817S (CTR B),"U1,U2,U3,U4",SOP-4_7.5x4.1mm_P2.54mm,C109227,LTV-817S-TA1-B,Lite-On,4

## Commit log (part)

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2026-02-15 ui clean up
2026-02-15 more format cleanup
2026-02-15 added contious jog
2026-02-15 inital gamepad support
2026-02-15 base config update
2026-02-16 inital probe support
2026-02-16 added icons
2026-02-16 adding build support for multiple platforms
2026-02-16 ui poisition cleanup
2026-02-17 ui theme cleanup
2026-02-17 Ui cleanup and lag fix
2026-02-17 probe layout cleanup
2026-02-17 more cleanup
2026-02-17 lots of work on render in attempt to show cut line and line segement select
2026-02-18 addeed app config UI
2026-02-18 added close to dialogs
2026-02-18 list box styling
2026-02-19 unit update
2026-02-19 more metric vs inch fixes
2026-02-19 added my unit to display
2026-02-19 more unit cleanup
2026-02-19 maybe last metric and imperial conversion
2026-02-19 removed extra probe signal and fix unit chnage
2026-02-19 remove unused using statements and file formate cleanup
2026-02-19 render perfromance improvements
2026-02-20 added job timer
2026-02-20 enabled design binding
2026-02-20 update job button states
2026-02-20 small refactor to excat dup code calculation into one state service object
2026-02-20 update to add poll rate to config and load png for spindle
2026-02-20 bug fixes with led states
2026-02-20 console update fixes
2026-02-20 update to add reconnect loop in connections
2026-02-20 reconnect logic for serial/tcp/websocket
2026-02-21 Sd card read/delete/ transfer supporting UI
2026-02-21 dialogs will be brought to front if minimized and dialog button pressed again
2026-02-21 push for build script fixes
2026-02-21 new pic
2026-02-21 added bordlerss mode and close application
2026-02-21 screen shots for welcome md
2026-02-21 Initialize README with project details and images
    Add project overview and initial documentation.
2026-02-21 more screen shots
2026-02-21 Revise README sections and images for better clarity
    Updated README to enhance clarity and organization of features.
2026-02-21 more screen captures for welcome md
2026-02-21 layout Cleanup
2026-02-22 ui based on Grbl state and connection state
2026-02-22 more screen captures
2026-02-22 prevent starting a second connection by clicking connect after connection was made
2026-02-22 add gamepad config and adjusted dialog statup location
2026-02-22 new screen captures for gamepad config
2026-02-22 image update
2026-02-22 Fix image path for Rapid-ATC in README
2026-02-22 layout cleanup for large file names
2026-02-22 adding config to turn off AA and so far noticable improvements by caching the sence as a bitmap vs vector redraw
2026-02-22 added config item to turn off Anit-Alias
2026-02-22 feed rate disaply unit fix
2026-02-22 initial checkin
2026-02-22 fixes for aux io
2026-02-23 cleanup
2026-02-23 update nugets for linux runtimes
2026-02-23 update pathing for linux
2026-02-23 more linux pathing fixes
2026-02-24 package dependency update
2026-02-24 clean to remove old artifacts
2026-02-24 more package updates
2026-02-24 font update to work on all platforms
2026-02-24 Ui cleanup for new text
2026-02-24 installer update
2026-02-24 more layout cleanup
2026-02-24 changed wording to clarify render optiions
2026-02-24 update to include spindle icon
2026-02-24 ui and adjusted theme for less animation
2026-02-25 added hardware based render
2026-02-25 fix for render control
2026-02-26 added tool change indicator
2026-02-26 update for styling
2026-02-27 fix for metric to imperial dro resizing
2026-02-27 adding verison check
2026-02-27 more ui cleanup
2026-02-28 set base config to use hardware render
2026-02-28 cleanup start up
2026-06-19 fix for setting and cleanup
2026-06-20 update to gcode viewer and console ouput
2026-06-20 sytax fix
2026-06-20 build update
2026-06-20 ui bud fix
2026-06-20 text format changes for macro section to match other controls
2026-06-21 fixes for location and closes
2026-06-21 gcode line highlight for processed line
2026-06-21 had more gcode highlighting
